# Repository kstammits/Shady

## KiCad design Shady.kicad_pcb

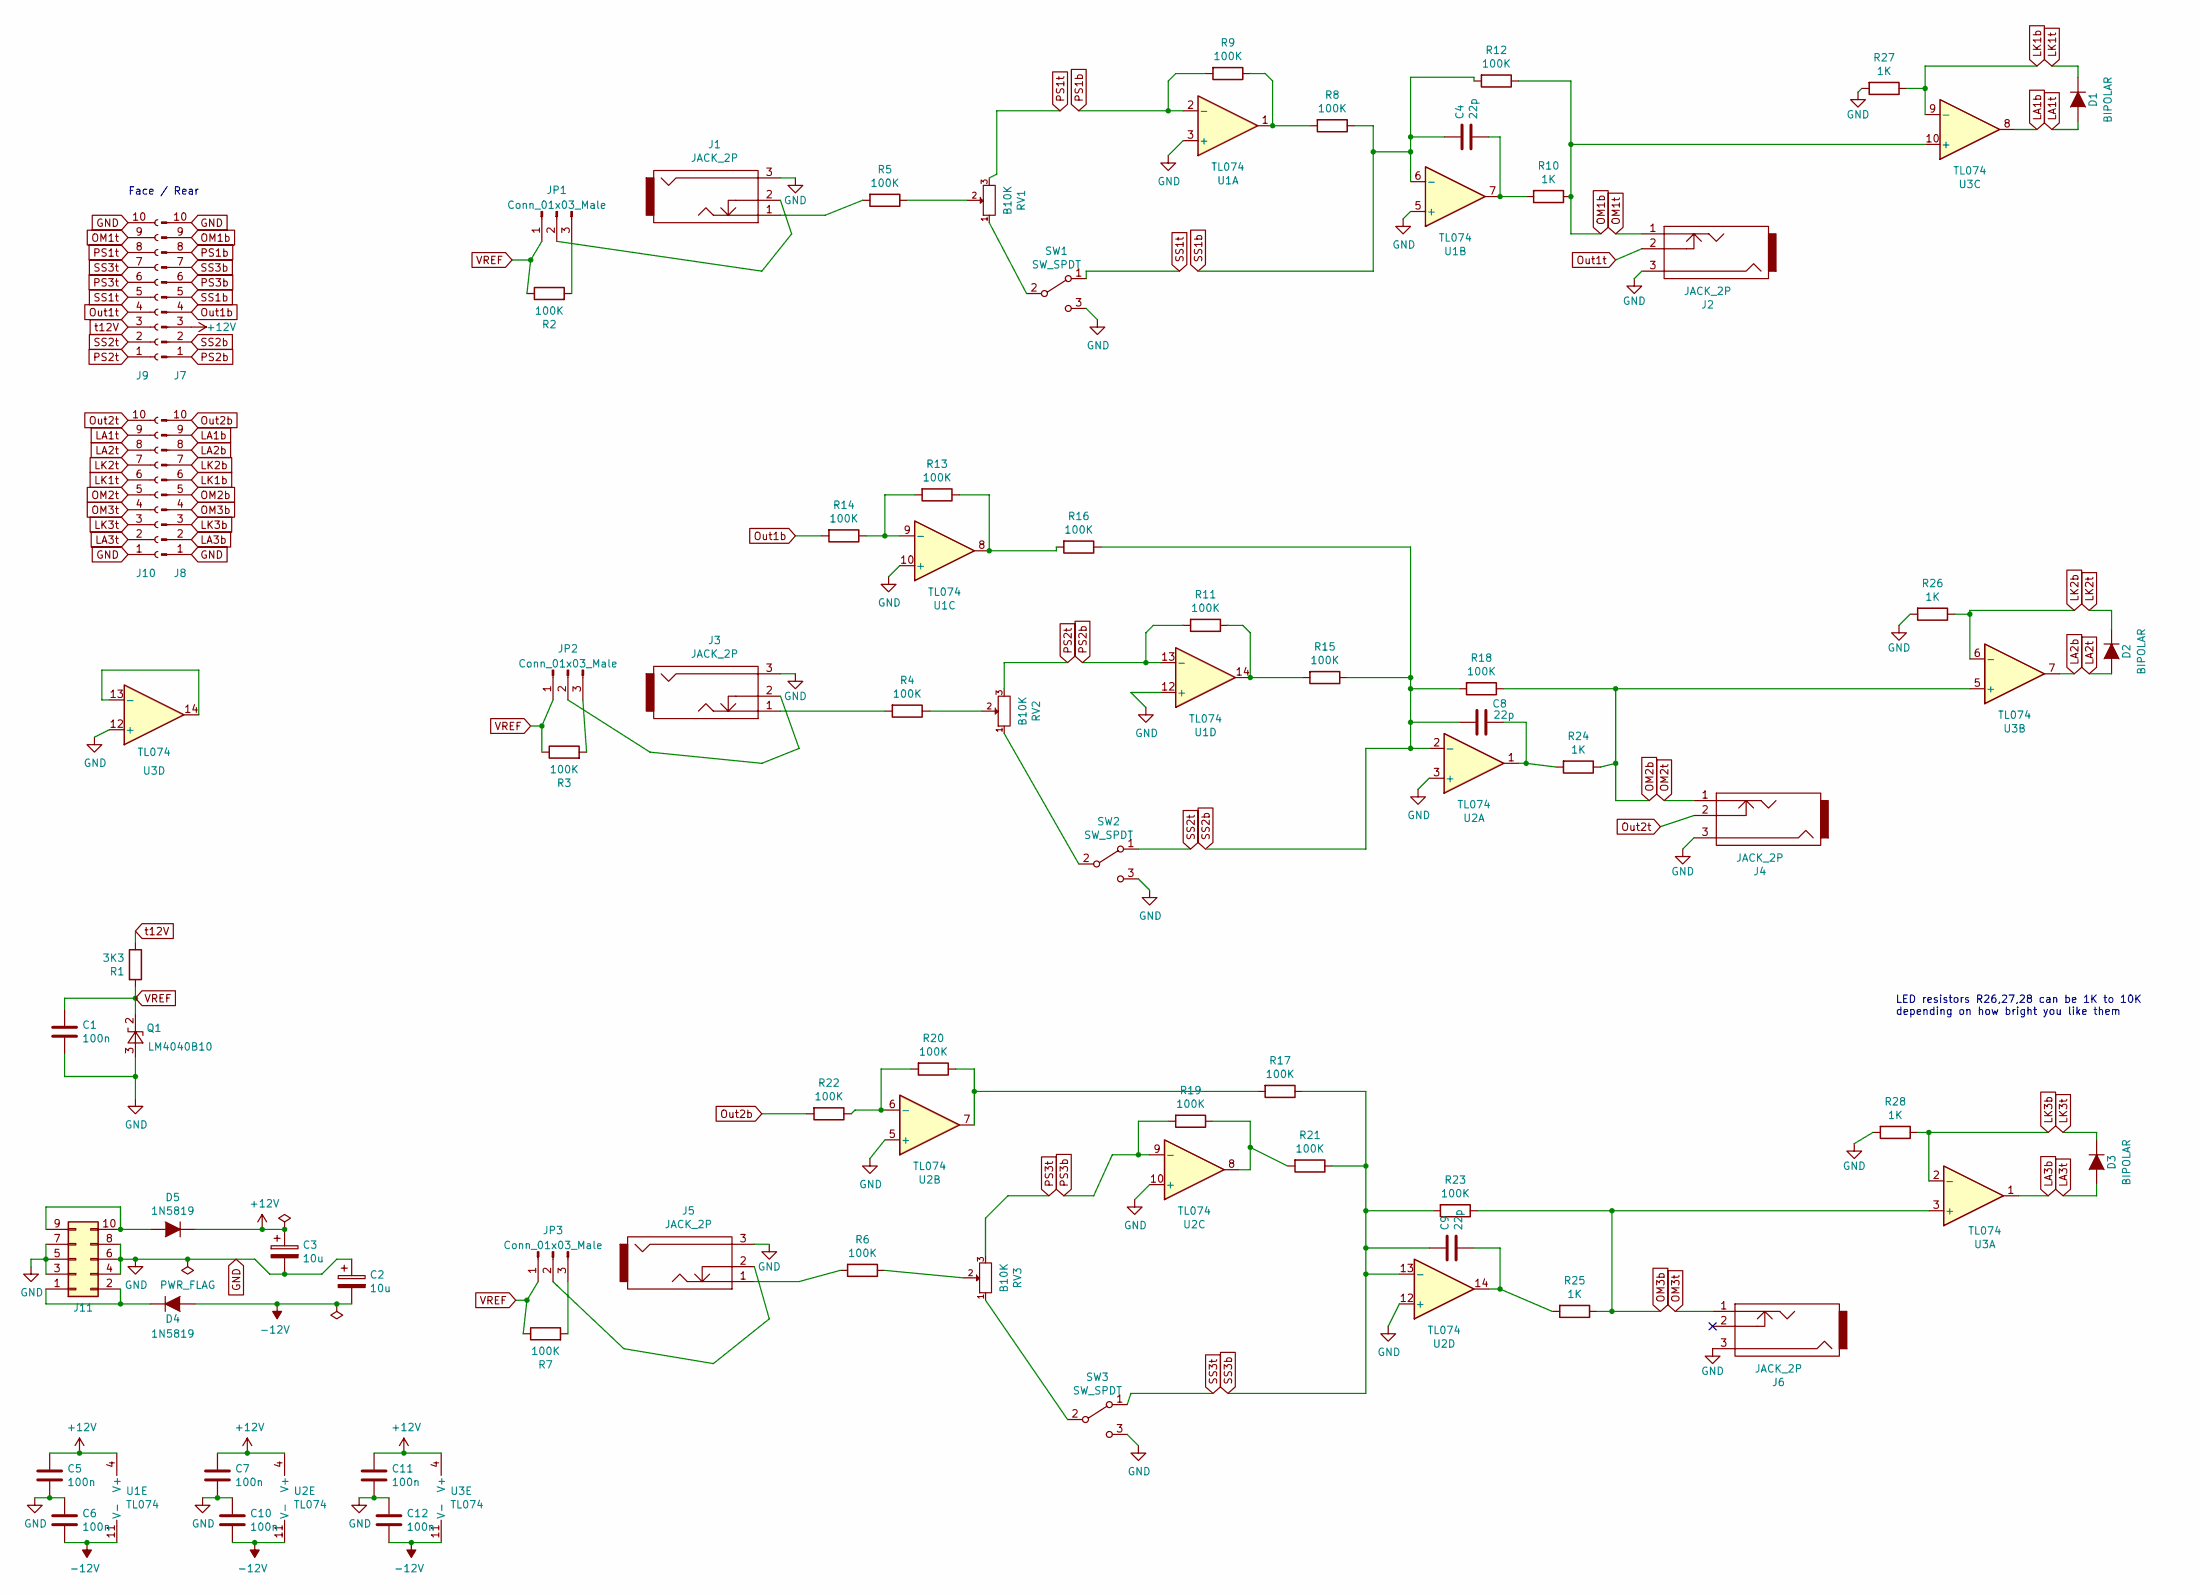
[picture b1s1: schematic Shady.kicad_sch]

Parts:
C1, C5, C6, C7, C10, C11, C12: 100n; C_Disc_D5.0mm_W2.5mm_P2.50mm
C2, C3: 10u; CP_Radial_D5.0mm_P2.50mm
C4, C8, C9: 22p; C_Disc_D3.0mm_W2.0mm_P2.50mm
D1, D2, D3: BIPOLAR; LED_D5.0mm
D4, D5: 1N5819; D_DO-41_SOD81_P10.16mm_Horizontal
J1, J2, J3, J4, J5, J6: JACK_2P; Thonkiconn
J7, J8: Conn_01x10_Male; PinHeader_1x10_P2.54mm_Vertical
J9, J10: Conn_01x10_Female; PinHeader_1x10_P2.54mm_Vertical
J11: Conn_02x05_Odd_Even; PinHeader_2x05_P2.54mm_Vertical
JP1, JP2, JP3: Conn_01x03_Male; PinHeader_1x03_P2.54mm_Horizontal
Q1: LM4040B10; TO-92_Inline_Wide
R1: 3K3; R_Axial_DIN0207_L6.3mm_D2.5mm_P2.54mm_Vertical
R2, R3, R4, R5, R6, R7, R8, R9, R11, R12, R13, R14, R15, R16, R17, R18, R19, R20, R21, R22, R23: 100K; R_Axial_DIN0207_L6.3mm_D2.5mm_P2.54mm_Vertical
R10, R24, R25, R26, R27, R28: 1K; R_Axial_DIN0207_L6.3mm_D2.5mm_P2.54mm_Vertical
RV1, RV2, RV3: B10K; Potentiometer_Alpha_RD901F-40-00D_Single_Vertical
SW1, SW2, SW3: SW_SPDT; SPDT_Tayda-A5111
U1, U2, U3: TL074; DIP-14_W7.62mm_Socket

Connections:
+12V: C3.1, C5.1, C7.1, C11.1, D5.1 (K), J7.3, U1.4 (V+), U2.4 (V+), U3.4 (V+)
-12V: C2.2, C6.2, C10.2, C12.2, D4.2 (A), U1.11 (V-), U2.11 (V-), U3.11 (V-)
GND: C1.2, C2.1, C3.2, C5.2, C6.1, C7.2, C10.1, C11.2, C12.1, J1.3, J2.3, J3.3, J4.3, J5.3, J6.3, J7.10, J8.1, J9.10, J10.1, J11.3, J11.4, J11.5, J11.6, J11.7, J11.8, Q1.3 (A), R26.2, R27.2, R28.2, SW1.3 (C), SW2.3 (C), SW3.3 (C), U1.3 (+), U1.5 (+), U1.10 (+), U1.12 (+), U2.3 (+), U2.5 (+), U2.10 (+), U2.12 (+), U3.12 (+)
LA1b: J8.9, U3.8
LA1t: D1.2 (A), J10.9
LA2b: J8.8, U3.7
LA2t: D2.2 (A), J10.8
LA3b: J8.2, U3.1
LA3t: D3.2 (A), J10.2
LK1b: J8.6, R27.1, U3.9 (-)
LK1t: D1.1 (K), J10.6
LK2b: J8.7, R26.1, U3.6 (-)
LK2t: D2.1 (K), J10.7
LK3b: J8.3, R28.1, U3.2 (-)
LK3t: D3.1 (K), J10.3
unnamed: C4.2, R10.2, U1.7
unnamed: C8.2, R24.2, U2.1
unnamed: C9.2, R25.2, U2.14
unnamed: D5.2 (A), J11.9, J11.10
unnamed: D4.1 (K), J11.1, J11.2
unnamed: J1.1, R5.2
unnamed: J1.2, JP1.2
unnamed: J3.1, R4.2
unnamed: J3.2, JP2.2
unnamed: J5.1, R6.2
unnamed: J5.2, JP3.2
unnamed: JP1.3, R2.2
unnamed: JP2.3, R3.2
unnamed: JP3.3, R7.2
unnamed: R5.1, RV1.2
unnamed: R13.2, R14.1, U1.9 (-)
unnamed: R8.2, R9.1, U1.1
unnamed: R13.1, R16.2, U1.8
unnamed: R11.1, R15.2, U1.14
unnamed: R4.1, RV2.2
unnamed: R17.2, R20.1, U2.7
unnamed: R20.2, R22.1, U2.6 (-)
unnamed: R19.1, R21.2, U2.8
unnamed: R6.1, RV3.2
unnamed: RV1.1, SW1.2 (B)
unnamed: RV2.1, SW2.2 (B)
unnamed: RV3.1, SW3.2 (B)
unnamed: U3.13 (-), U3.14
OM1b: J7.9, R10.1, R12.1, U3.10 (+)
OM1t: J2.1, J9.9
OM2b: J8.5, R18.1, R24.1, U3.5 (+)
OM2t: J4.1, J10.5
OM3b: J8.4, R23.1, R25.1, U3.3 (+)
OM3t: J6.1, J10.4
Out1b: J7.4, R14.2
Out1t: J2.2, J9.4
Out2b: J8.10, R22.2
Out2t: J4.2, J10.10
PS1b: J7.8, R9.2, U1.2 (-)
PS1t: J9.8, RV1.3
PS2b: J7.1, R11.2, U1.13 (-)
PS2t: J9.1, RV2.3
PS3b: J7.6, R19.2, U2.9 (-)
PS3t: J9.6, RV3.3
SS1b: C4.1, J7.5, R8.1, R12.2, U1.6 (-)
SS1t: J9.5, SW1.1 (A)
SS2b: C8.1, J7.2, R15.1, R16.1, R18.2, U2.2 (-)
SS2t: J9.2, SW2.1 (A)
SS3b: C9.1, J7.7, R17.1, R21.1, R23.2, U2.13 (-)
SS3t: J9.7, SW3.1 (A)
VREF: C1.1, JP1.1, JP2.1, JP3.1, Q1.2 (K), R1.2, R2.1, R3.1, R7.1
t12V: J9.3, R1.1

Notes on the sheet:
LED resistors R26,27,28 can be 1K to 10K depending on how bright you like them
Face / Rear

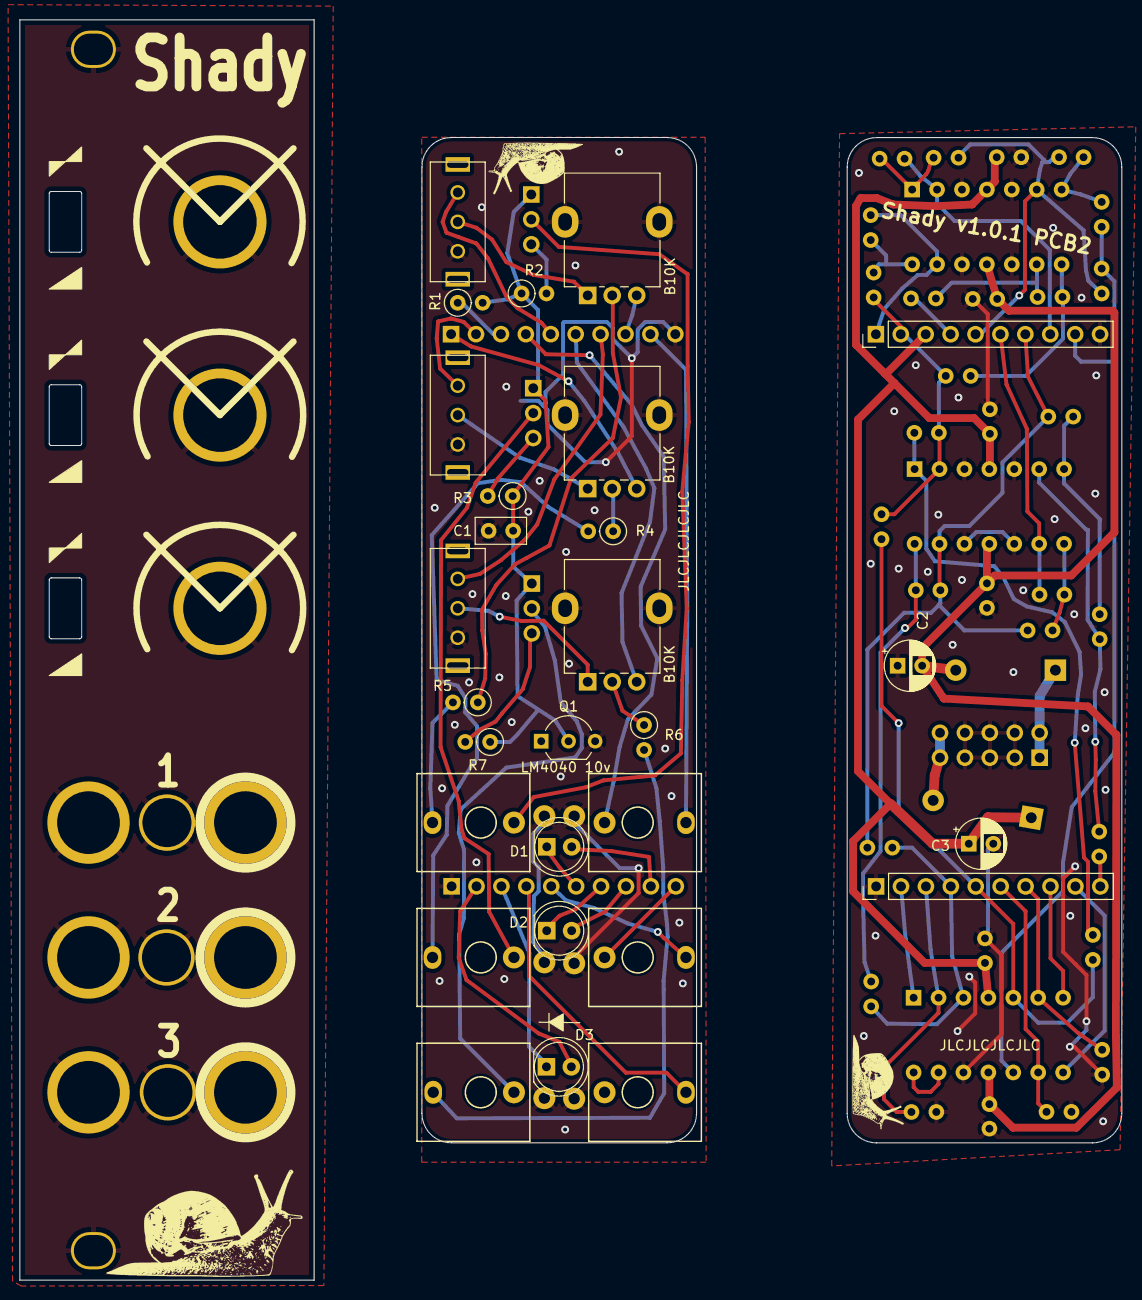
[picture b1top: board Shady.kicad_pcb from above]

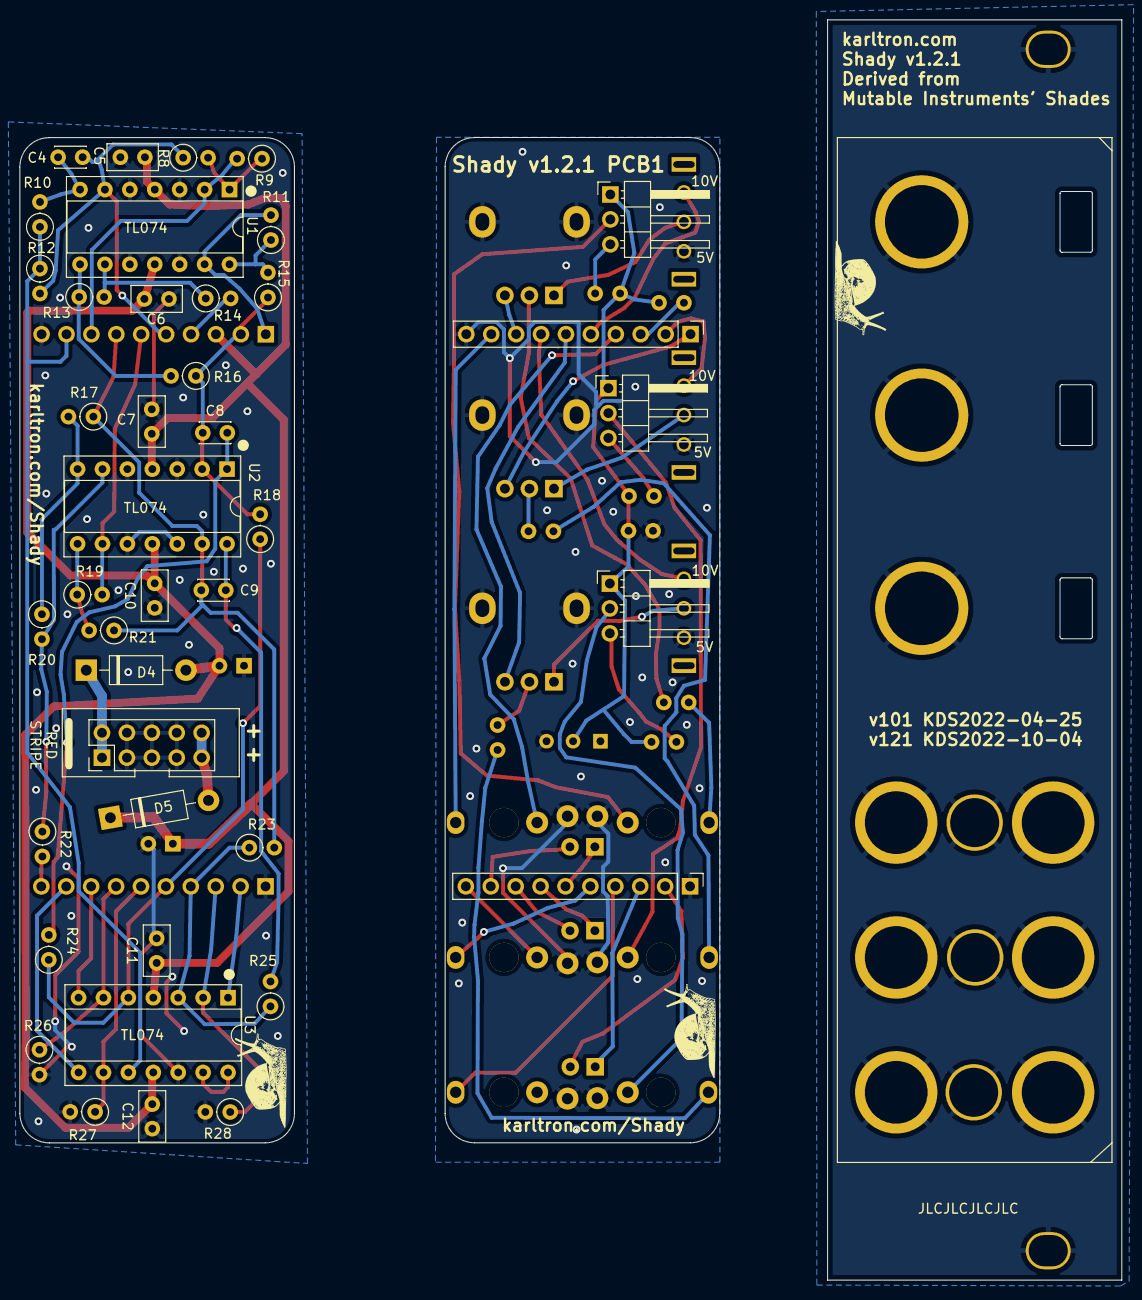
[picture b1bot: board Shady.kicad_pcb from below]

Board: 2 copper layers, 112.4 x 128.5 mm, 73 parts (43 on the bottom side), 67 nets.

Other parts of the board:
G1, G2, G3, G4: Logo_Open_Hardware_Small; snail4.sm

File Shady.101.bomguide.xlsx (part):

Source: | /Users/karl/Workspace/KiCad/Shady/Shady/Shady.kicad_sch
Date: | Wednesday, April 27, 2022 at 03:17:39 PM
Tool: | Eeschema (6.0.2-0)
Generator: | /Applications/KiCad/KiCad.app/Contents/SharedSupport/plugins/bom_csv_grouped_by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
Component Count: | 69
Individual Components:
Item | Qty | Reference(s) | Value | LibPart | Footprint | Datasheet
 |  | C1 | 100n | device:C | Capacitor_THT:C_Disc_D5.0mm_W2.5mm_P2.50mm
 |  | C2 | 10u | Device:CP | Capacitor_THT:CP_Radial_D5.0mm_P2.50mm
 |  | C3 | 10u | Device:CP | Capacitor_THT:CP_Radial_D5.0mm_P2.50mm
 |  | C4 | 22p | device:C | Capacitor_THT:C_Disc_D3.0mm_W2.0mm_P2.50mm
 |  | C5 | 100n | device:C | Capacitor_THT:C_Disc_D5.0mm_W2.5mm_P2.50mm
 |  | C6 | 100n | device:C | Capacitor_THT:C_Disc_D5.0mm_W2.5mm_P2.50mm
 |  | C7 | 100n | device:C | Capacitor_THT:C_Disc_D5.0mm_W2.5mm_P2.50mm
 |  | C8 | 22p | device:C | Capacitor_THT:C_Disc_D3.0mm_W2.0mm_P2.50mm
 |  | C9 | 22p | device:C | Capacitor_THT:C_Disc_D3.0mm_W2.0mm_P2.50mm
 |  | C10 | 100n | device:C | Capacitor_THT:C_Disc_D5.0mm_W2.5mm_P2.50mm
 |  | C11 | 100n | device:C | Capacitor_THT:C_Disc_D5.0mm_W2.5mm_P2.50mm
 |  | C12 | 100n | device:C | Capacitor_THT:C_Disc_D5.0mm_W2.5mm_P2.50mm
 |  | D1 | BIPOLAR | device:D | LED_THT:LED_D5.0mm
 |  | D2 | BIPOLAR | device:D | LED_THT:LED_D5.0mm
 |  | D3 | BIPOLAR | device:D | LED_THT:LED_D5.0mm
 |  | D4 | 1N5819 | device:D | Diode_THT:D_DO-41_SOD81_P10.16mm_Horizontal
 |  | D5 | 1N5819 | device:D | Diode_THT:D_DO-41_SOD81_P10.16mm_Horizontal
 |  | J1 | JACK_2P | device:JACK_2P | europi:Thonkiconn
 |  | J2 | JACK_2P | device:JACK_2P | europi:Thonkiconn
 |  | J3 | JACK_2P | device:JACK_2P | europi:Thonkiconn
 |  | J4 | JACK_2P | device:JACK_2P | europi:Thonkiconn
 |  | J5 | JACK_2P | device:JACK_2P | europi:Thonkiconn
 |  | J6 | JACK_2P | device:JACK_2P | europi:Thonkiconn
 |  | J7 | Conn_01x10_Male | Connector:Conn_01x10_Male | Connector_PinHeader_2.54mm:PinHeader_1x10_P2.54mm_Vertical | ~
 |  | J8 | Conn_01x10_Male | Connector:Conn_01x10_Male | Connector_PinHeader_2.54mm:PinHeader_1x10_P2.54mm_Vertical | ~
 |  | J9 | Conn_01x10_Female | Connector:Conn_01x10_Female | Connector_PinHeader_2.54mm:PinHeader_1x10_P2.54mm_Vertical | ~
 |  | J10 | Conn_01x10_Female | Connector:Conn_01x10_Female | Connector_PinHeader_2.54mm:PinHeader_1x10_P2.54mm_Vertical | ~
 |  | J11 | Conn_02x05_Odd_Even | Connector_Generic:Conn_02x05_Odd_Even | Connector_PinHeader_2.54mm:PinHeader_2x05_P2.54mm_Vertical | ~
 |  | JP1 | Conn_01x03_Male | Connector:Conn_01x03_Male | Connector_PinHeader_2.54mm:PinHeader_1x03_P2.54mm_Horizontal | ~
 |  | JP2 | Conn_01x03_Male | Connector:Conn_01x03_Male | Connector_PinHeader_2.54mm:PinHeader_1x03_P2.54mm_Horizontal | ~
 |  | JP3 | Conn_01x03_Male | Connector:Conn_01x03_Male | Connector_PinHeader_2.54mm:PinHeader_1x03_P2.54mm_Horizontal | ~
 |  | Q1 | LM4040B10 | Reference_Voltage:LM4040LP-10 | Package_TO_SOT_THT:TO-92_Inline_Wide | http://www.ti.com/lit/ds/symlink/lm4040-n.pdf
 |  | R1 | 3K3 | device:R | Resistor_THT:R_Axial_DIN0207_L6.3mm_D2.5mm_P2.54mm_Vertical
 |  | R2 | 100K | device:R | Resistor_THT:R_Axial_DIN0207_L6.3mm_D2.5mm_P2.54mm_Vertical
 |  | R3 | 100K | device:R | Resistor_THT:R_Axial_DIN0207_L6.3mm_D2.5mm_P2.54mm_Vertical
 |  | R4 | 100K | device:R | Resistor_THT:R_Axial_DIN0207_L6.3mm_D2.5mm_P2.54mm_Vertical
 |  | R5 | 100K | device:R | Resistor_THT:R_Axial_DIN0207_L6.3mm_D2.5mm_P2.54mm_Vertical
 |  | R6 | 100K | device:R | Resistor_THT:R_Axial_DIN0207_L6.3mm_D2.5mm_P2.54mm_Vertical
 |  | R7 | 100K | device:R | Resistor_THT:R_Axial_DIN0207_L6.3mm_D2.5mm_P2.54mm_Vertical
 |  | R8 | 100K | device:R | Resistor_THT:R_Axial_DIN0207_L6.3mm_D2.5mm_P2.54mm_Vertical
 |  | R9 | 100K | device:R | Resistor_THT:R_Axial_DIN0207_L6.3mm_D2.5mm_P2.54mm_Vertical
 |  | R10 | 1K | device:R | Resistor_THT:R_Axial_DIN0207_L6.3mm_D2.5mm_P2.54mm_Vertical
 |  | R11 | 100K | device:R | Resistor_THT:R_Axial_DIN0207_L6.3mm_D2.5mm_P2.54mm_Vertical
 |  | R12 | 100K | device:R | Resistor_THT:R_Axial_DIN0207_L6.3mm_D2.5mm_P2.54mm_Vertical
 |  | R13 | 100K | device:R | Resistor_THT:R_Axial_DIN0207_L6.3mm_D2.5mm_P2.54mm_Vertical
 |  | R14 | 100K | device:R | Resistor_THT:R_Axial_DIN0207_L6.3mm_D2.5mm_P2.54mm_Vertical
 |  | R15 | 100K | device:R | Resistor_THT:R_Axial_DIN0207_L6.3mm_D2.5mm_P2.54mm_Vertical
 |  | R16 | 100K | device:R | Resistor_THT:R_Axial_DIN0207_L6.3mm_D2.5mm_P2.54mm_Vertical
 |  | R17 | 100K | device:R | Resistor_THT:R_Axial_DIN0207_L6.3mm_D2.5mm_P2.54mm_Vertical
 |  | R18 | 100K | device:R | Resistor_THT:R_Axial_DIN0207_L6.3mm_D2.5mm_P2.54mm_Vertical
 |  | R19 | 100K | device:R | Resistor_THT:R_Axial_DIN0207_L6.3mm_D2.5mm_P2.54mm_Vertical
 |  | R20 | 100K | device:R | Resistor_THT:R_Axial_DIN0207_L6.3mm_D2.5mm_P2.54mm_Vertical
 |  | R21 | 100K | device:R | Resistor_THT:R_Axial_DIN0207_L6.3mm_D2.5mm_P2.54mm_Vertical
 |  | R22 | 100K | device:R | Resistor_THT:R_Axial_DIN0207_L6.3mm_D2.5mm_P2.54mm_Vertical
 |  | R23 | 100K | device:R | Resistor_THT:R_Axial_DIN0207_L6.3mm_D2.5mm_P2.54mm_Vertical
 |  | R24 | 1K | device:R | Resistor_THT:R_Axial_DIN0207_L6.3mm_D2.5mm_P2.54mm_Vertical
 |  | R25 | 1K | device:R | Resistor_THT:R_Axial_DIN0207_L6.3mm_D2.5mm_P2.54mm_Vertical
 |  | R26 | 33K | device:R | Resistor_THT:R_Axial_DIN0207_L6.3mm_D2.5mm_P2.54mm_Vertical
 |  | R27 | 33K | device:R | Resistor_THT:R_Axial_DIN0207_L6.3mm_D2.5mm_P2.54mm_Vertical
 |  | R28 | 33K | device:R | Resistor_THT:R_Axial_DIN0207_L6.3mm_D2.5mm_P2.54mm_Vertical
 |  | RV1 | B10K | device:POT | Potentiometer_THT:Potentiometer_Alpha_RD901F-40-00D_Single_Vertical
 |  | RV2 | B10K | device:POT | Potentiometer_THT:Potentiometer_Alpha_RD901F-40-00D_Single_Vertical
 |  | RV3 | B10K | device:POT | Potentiometer_THT:Potentiometer_Alpha_RD901F-40-00D_Single_Vertical
 |  | SW1 | SW_SPDT | Switch:SW_SPDT | Cust:SPDT_Tayda-A5111 | ~
 |  | SW2 | SW_SPDT | Switch:SW_SPDT | Cust:SPDT_Tayda-A5111 | ~
 |  | SW3 | SW_SPDT | Switch:SW_SPDT | Cust:SPDT_Tayda-A5111 | ~
 |  | U1 | TL074 | Amplifier_Operational:TL074 | Package_DIP:DIP-14_W7.62mm_Socket | http://www.ti.com/lit/ds/symlink/tl071.pdf
 |  | U2 | TL074 | Amplifier_Operational:TL074 | Package_DIP:DIP-14_W7.62mm_Socket | http://www.ti.com/lit/ds/symlink/tl071.pdf
 |  | U3 | TL074 | Amplifier_Operational:TL074 | Package_DIP:DIP-14_W7.62mm_Socket | http://www.ti.com/lit/ds/symlink/tl071.pdf
Collated Components:
Item | Qty | Reference(s) | Value | LibPart | Footprint | Datasheet
1 | 7 | C1, C5, C6, C7, C10, C11, C12 | 100n | device:C | Capacitor_THT:C_Disc_D5.0mm_W2.5mm_P2.50mm
2 | 2 | C2, C3 | 10u | Device:CP | Capacitor_THT:CP_Radial_D5.0mm_P2.50mm
3 | 3 | C4, C8, C9 | 22p | device:C | Capacitor_THT:C_Disc_D3.0mm_W2.0mm_P2.50mm
4 | 3 | D1, D2, D3 | BIPOLAR | device:D | LED_THT:LED_D5.0mm
5 | 2 | D4, D5 | 1N5819 | device:D | Diode_THT:D_DO-41_SOD81_P10.16mm_Horizontal
6 | 6 | J1, J2, J3, J4, J5, J6 | JACK_2P | device:JACK_2P | europi:Thonkiconn
7 | 2 | J7, J8 | Conn_01x10_Male | Connector:Conn_01x10_Male | Connector_PinHeader_2.54mm:PinHeader_1x10_P2.54mm_Vertical | ~
8 | 2 | J9, J10 | Conn_01x10_Female | Connector:Conn_01x10_Female | Connector_PinHeader_2.54mm:PinHeader_1x10_P2.54mm_Vertical | ~
9 | 1 | J11 | Conn_02x05_Odd_Even | Connector_Generic:Conn_02x05_Odd_Even | Connector_PinHeader_2.54mm:PinHeader_2x05_P2.54mm_Vertical | ~
10 | 3 | JP1, JP2, JP3 | Conn_01x03_Male | Connector:Conn_01x03_Male | Connector_PinHeader_2.54mm:PinHeader_1x03_P2.54mm_Horizontal | ~
11 | 1 | Q1 | LM4040B10 | Reference_Voltage:LM4040LP-10 | Package_TO_SOT_THT:TO-92_Inline_Wide | http://www.ti.com/lit/ds/symlink/lm4040-n.pdf
12 | 1 | R1 | 3K3 | device:R | Resistor_THT:R_Axial_DIN0207_L6.3mm_D2.5mm_P2.54mm_Vertical
13 | 21 | R2, R3, R4, R5, R6, R7, R8, R9, R11, R12, R13, R14, R15, R16, R17, R18, R19, R2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 | 100K | device:R | Resistor_THT:R_Axial_DIN0207_L6.3mm_D2.5mm_P2.54mm_Vertical
14 | 3 | R10, R24, R25 | 1K | device:R | Resistor_THT:R_Axial_DIN0207_L6.3mm_D2.5mm_P2.54mm_Vertical
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
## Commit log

2022-04-26 initial commit
    version 1.0.1 of the board complete, might be working but untested
2022-04-27 updates for rev101
2022-04-27 Update .gitignore
    git ignore binaries
2022-08-07 v111
    v111 has some triangles on the faceplate
2022-10-07 update to v121
    switched the switches around so it matches original better
    adjusted logos on front panel
2022-11-19 rearrange steps
    update instructions for easier builds
